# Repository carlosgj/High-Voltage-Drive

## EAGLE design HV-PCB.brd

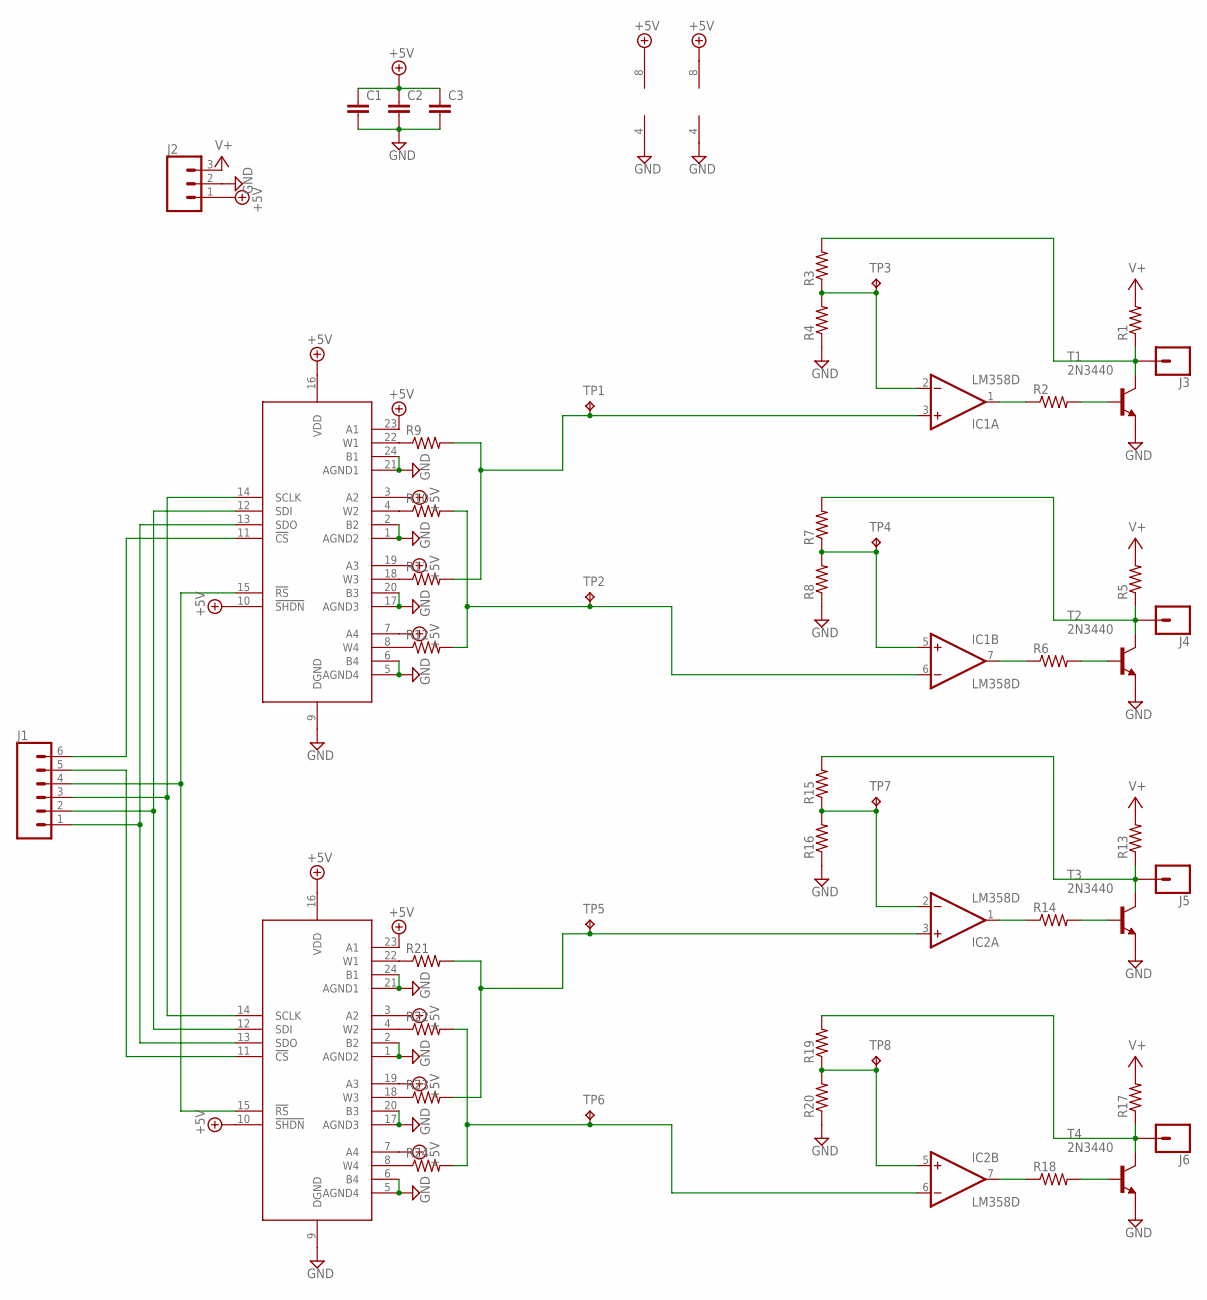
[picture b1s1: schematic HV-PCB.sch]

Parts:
C1, C2, C3: C-EUC1206K; C1206K
IC1, IC2: LM358D; SO08
J1: CONN_06SILK_FEMALE_PTH; 1X06
J2: CONN_03; 1X03
J3, J4, J5, J6: CONN_01; 1X01
R1, R2, R3, R4, R5, R6, R7, R8, R9, R10, R11, R12, R13, R14, R15, R16, R17, R18, R19, R20, R21, R22, R23, R24: R-US_M1206; M1206
T1, T2, T3, T4: 2N3440; TO5
TP1, TP2, TP3, TP4, TP5, TP6, TP7, TP8: TPB1,27; B1,27
U$1, U$2: AD8403; SO24L

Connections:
!RST: J1.4, U$1.15 (!RS), U$2.15 (!RS)
+5V: C1.1, C2.1, C3.1, IC1.8 (V+), IC2.8 (V+), J2.1, U$1.3 (A2), U$1.7 (A4), U$1.10 (!SHDN), U$1.16 (VDD), U$1.19 (A3), U$1.23 (A1), U$2.3 (A2), U$2.7 (A4), U$2.10 (!SHDN), U$2.16 (VDD), U$2.19 (A3), U$2.23 (A1)
GND: C1.2, C2.2, C3.2, IC1.4 (V-), IC2.4 (V-), J2.2, R4.1, R8.1, R16.1, R20.1, T1.1 (E), T2.1 (E), T3.1 (E), T4.1 (E), U$1.1 (AGND2), U$1.2 (B2), U$1.5 (AGND4), U$1.6 (B4), U$1.9 (DGND), U$1.17 (AGND3), U$1.20 (B3), U$1.21 (AGND1), U$1.24 (B1), U$2.1 (AGND2), U$2.2 (B2), U$2.5 (AGND4), U$2.6 (B4), U$2.9 (DGND), U$2.17 (AGND3), U$2.20 (B3), U$2.21 (AGND1), U$2.24 (B1)
unnamed: J3.1, R1.1, R3.2, T1.3 (C)
unnamed: R2.2, T1.2 (B)
unnamed: IC1.1 (OUT), R2.1
unnamed: IC1.2 (-IN), R3.1, R4.2, TP3.TP
unnamed: J4.1, R5.1, R7.2, T2.3 (C)
unnamed: R6.2, T2.2 (B)
unnamed: IC1.7 (OUT), R6.1
unnamed: IC1.5 (+IN), R7.1, R8.2, TP4.TP
unnamed: R9.1, U$1.22 (W1)
unnamed: R10.1, U$1.4 (W2)
unnamed: IC1.3 (+IN), R9.2, R11.2, TP1.TP
unnamed: IC1.6 (-IN), R10.2, R12.2, TP2.TP
unnamed: R11.1, U$1.18 (W3)
unnamed: R12.1, U$1.8 (W4)
unnamed: J5.1, R13.1, R15.2, T3.3 (C)
unnamed: R14.2, T3.2 (B)
unnamed: IC2.1 (OUT), R14.1
unnamed: IC2.2 (-IN), R15.1, R16.2, TP7.TP
unnamed: J6.1, R17.1, R19.2, T4.3 (C)
unnamed: R18.2, T4.2 (B)
unnamed: IC2.7 (OUT), R18.1
unnamed: IC2.5 (+IN), R19.1, R20.2, TP8.TP
unnamed: R21.1, U$2.22 (W1)
unnamed: R22.1, U$2.4 (W2)
unnamed: IC2.3 (+IN), R21.2, R23.2, TP5.TP
unnamed: R23.1, U$2.18 (W3)
unnamed: R24.1, U$2.8 (W4)
unnamed: IC2.6 (-IN), R22.2, R24.2, TP6.TP
unnamed: J1.5, U$2.11 (!CS)
unnamed: J1.6, U$1.11 (!CS)
SCLK: J1.3, U$1.14 (SCLK), U$2.14 (SCLK)
SDI: J1.2, U$1.12 (SDI), U$2.12 (SDI)
SDO: J1.1, U$1.13 (SDO), U$2.13 (SDO)
V+: J2.3, R1.2, R5.2, R13.2, R17.2

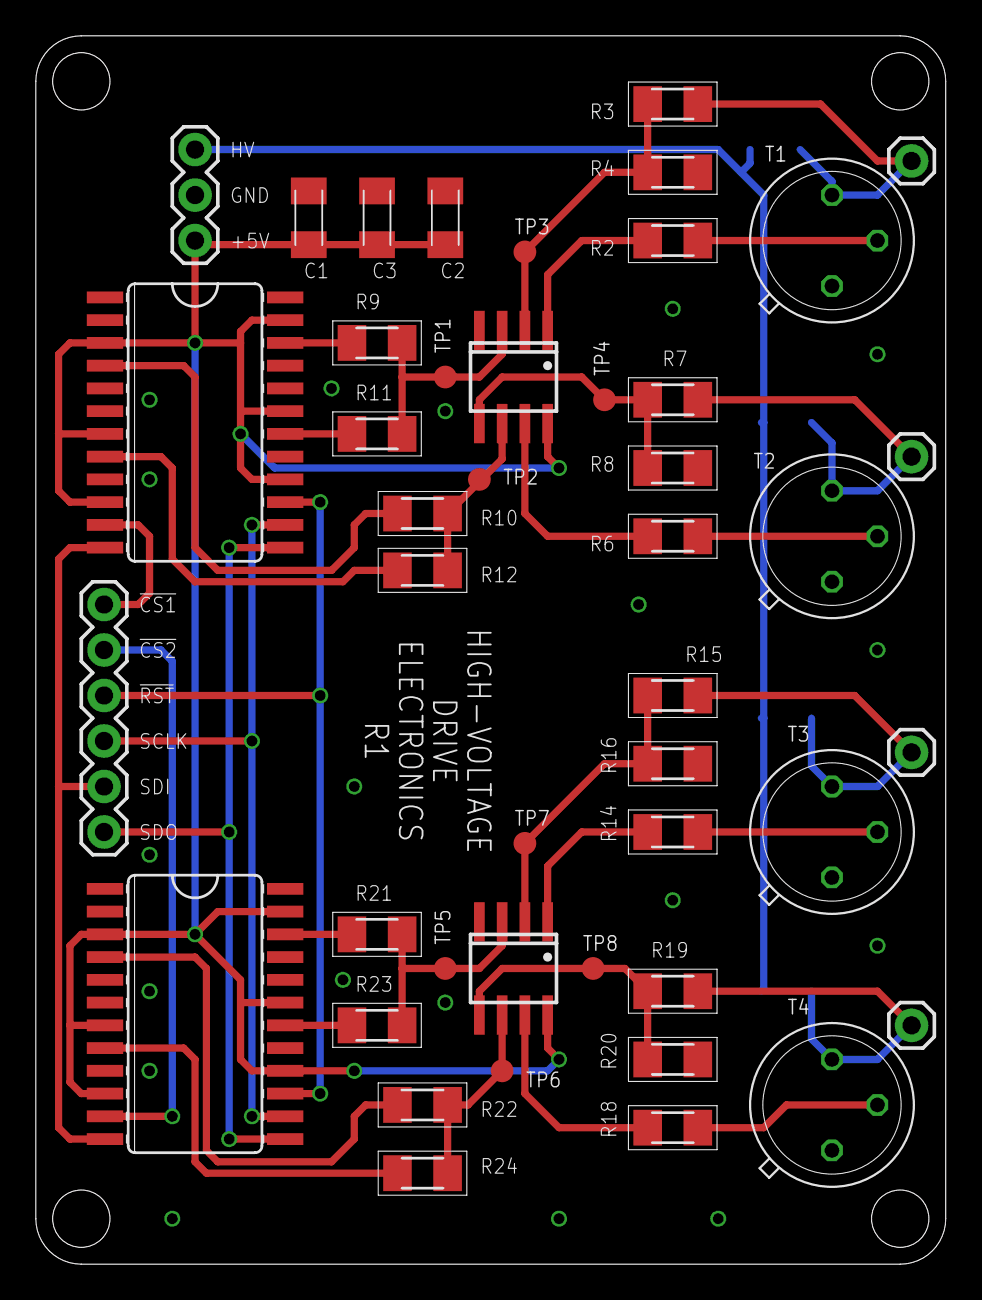
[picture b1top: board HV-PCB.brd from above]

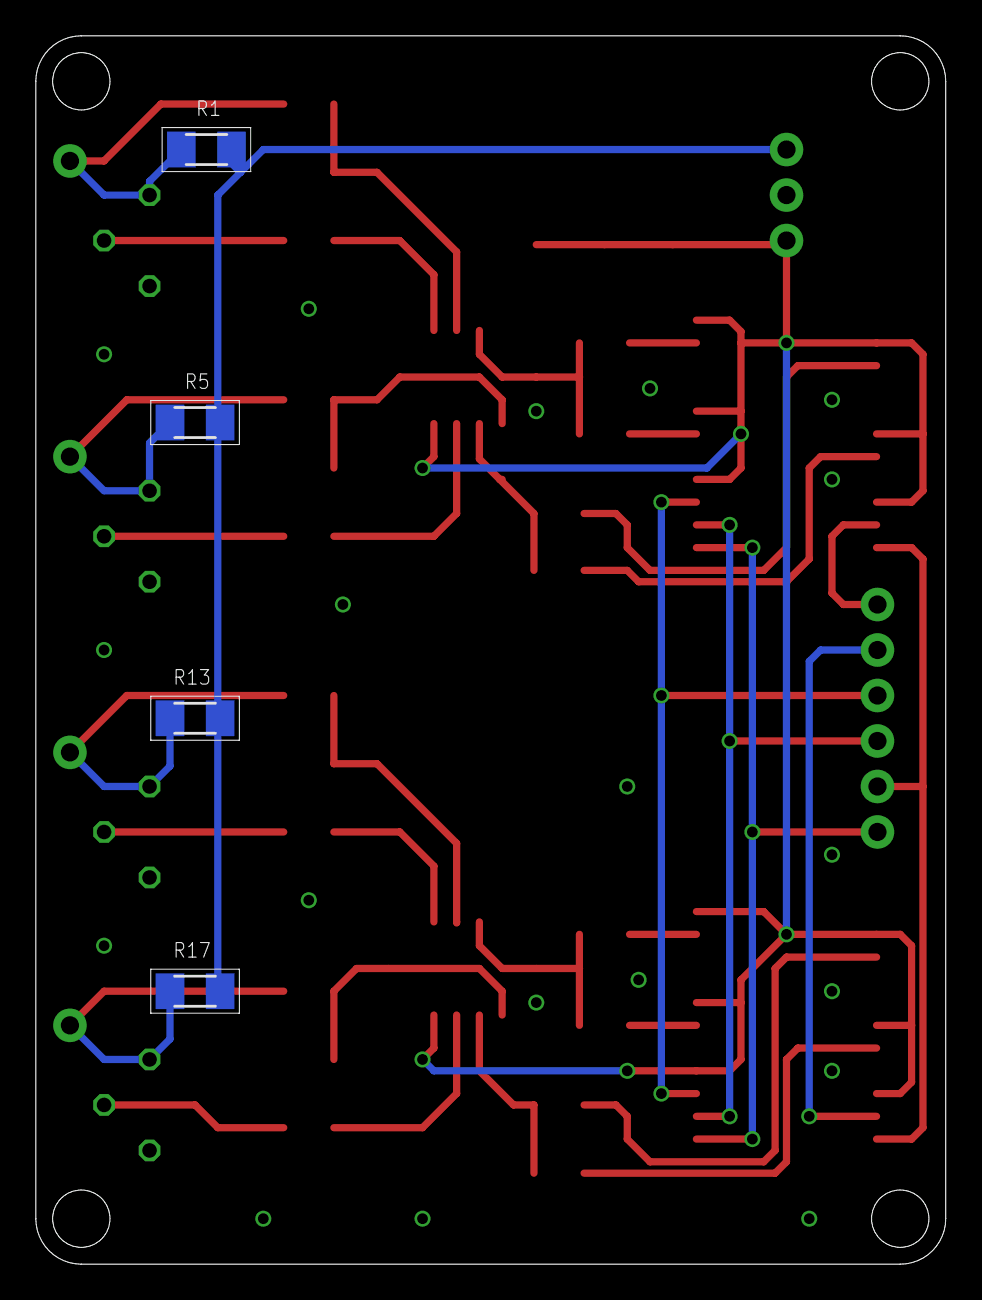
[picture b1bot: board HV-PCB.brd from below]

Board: 2 copper layers, 50.8 x 68.6 mm, 49 parts (4 on the bottom side), 37 nets.

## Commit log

2021-03-06 HV board r1

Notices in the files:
parts and their libraries:
SparkFun-Connectors: Licensing: Creative Commons ShareAlike 4.0 International - https://creativecommons.org/licenses/by-sa/4.0
